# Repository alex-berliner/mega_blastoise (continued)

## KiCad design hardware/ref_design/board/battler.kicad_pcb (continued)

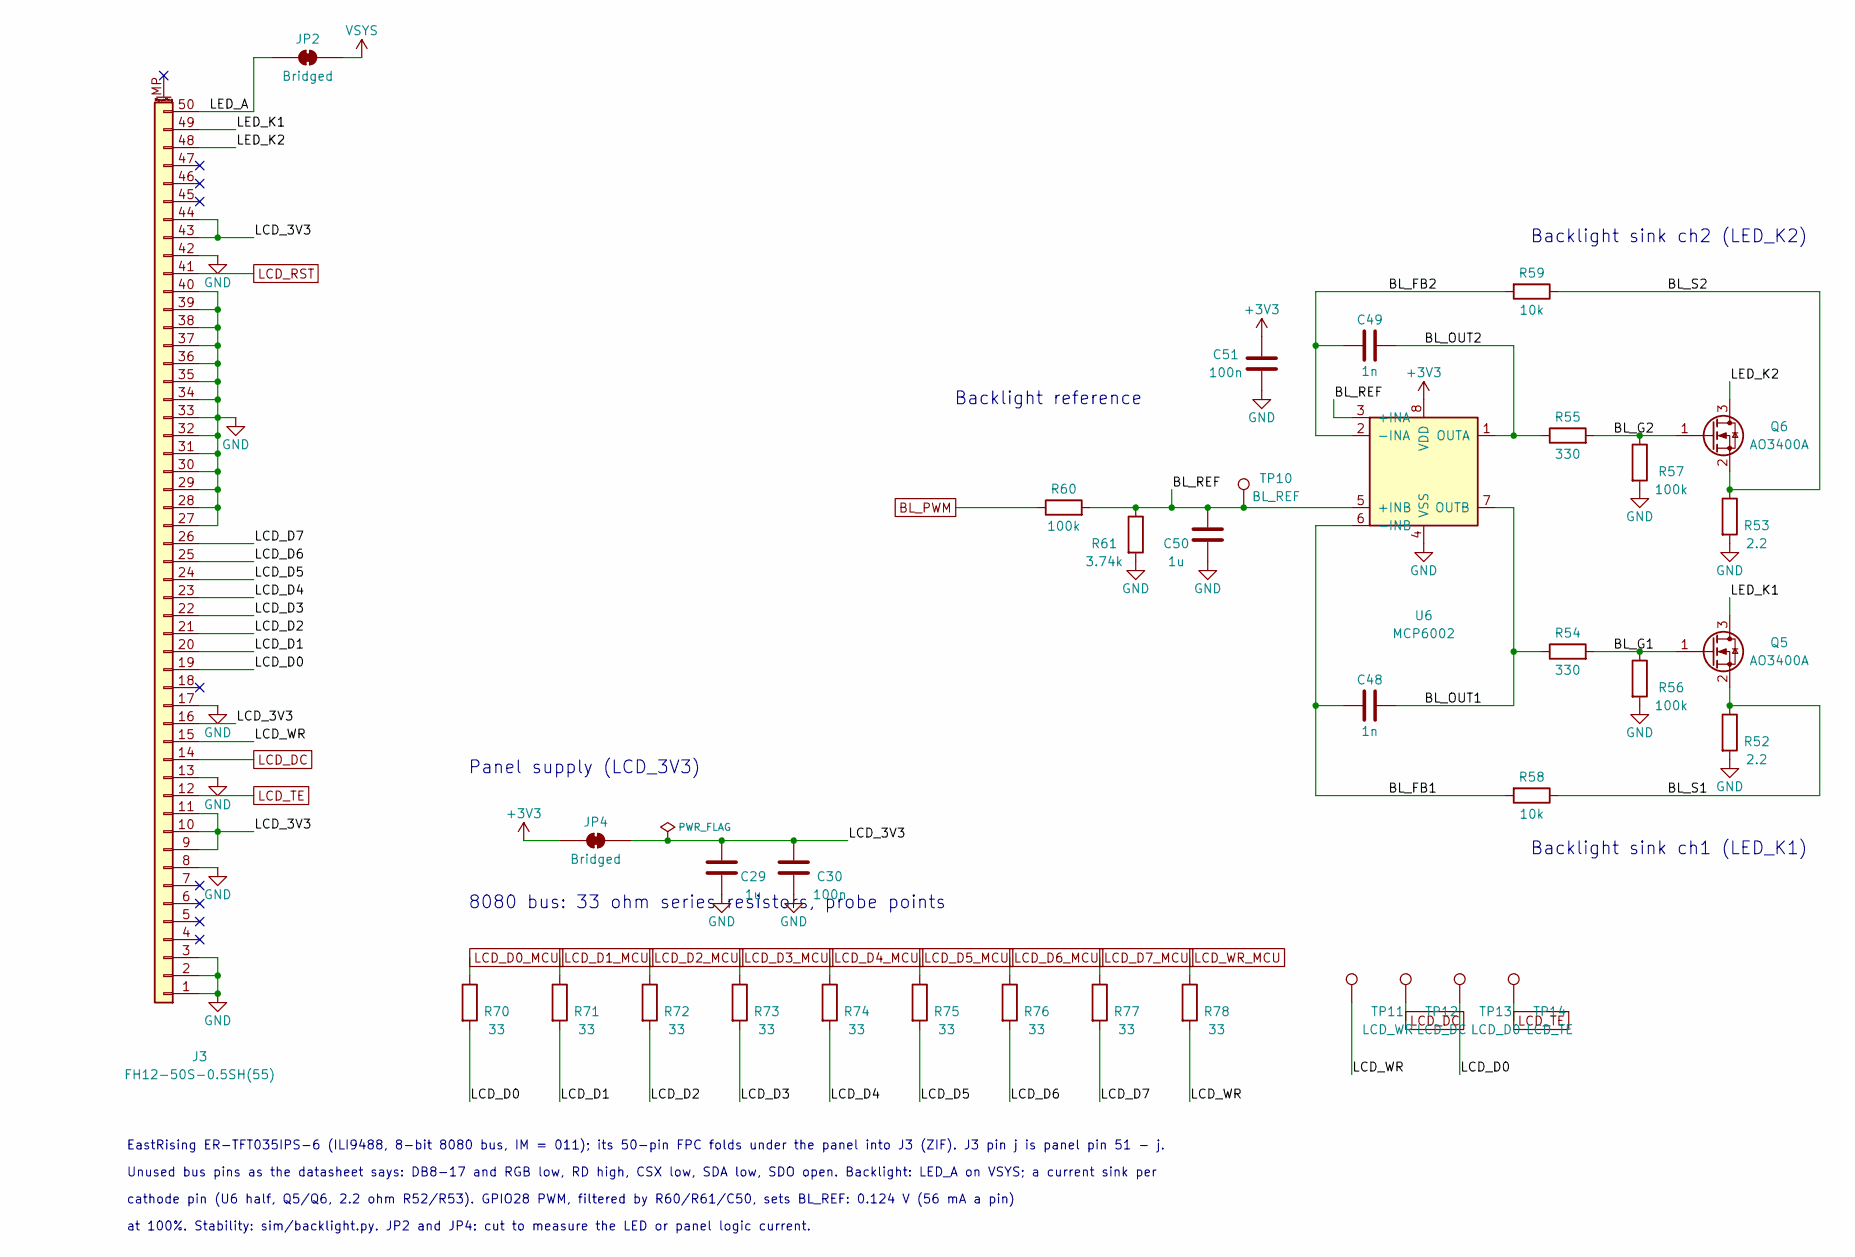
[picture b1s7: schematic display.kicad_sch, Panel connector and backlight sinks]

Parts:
C29, C50: 1u; C_0402_1005Metric; MPN CL05A105KA5NQNC; LCSC C52923
C30, C51: 100n; C_0402_1005Metric; MPN CL05B104KO5NNNC; LCSC C1525
C48, C49: 1n; C_0402_1005Metric; MPN 0402B102K500NT; LCSC C1523
J3: FH12-50S-0.5SH(55); Hirose_FH12-50S-0.5SH_1x50-1MP_P0.50mm_Horizontal; MPN FH12-50S-0.5SH(55); LCSC C202116
JP2, JP4: Bridged; SolderJumper-2_P1.3mm_Bridged_Pad1.0x1.5mm
Q5, Q6: AO3400A; SOT-23; MPN AO3400A; LCSC C20917
R52, R53: 2.2; R_0603_1608Metric; MPN 0603WAF220KT5E; LCSC C22939
R54, R55: 330; R_0402_1005Metric; MPN 0402WGF3300TCE; LCSC C25104
R56, R57, R60: 100k; R_0402_1005Metric; MPN 0402WGF1003TCE; LCSC C25741
R58, R59: 10k; R_0402_1005Metric; MPN 0402WGF1002TCE; LCSC C25744
R61: 3.74k; R_0402_1005Metric; MPN 0402WGF3741TCE; LCSC C15172
R70, R71, R72, R73, R74, R75, R76, R77, R78: 33; R_0402_1005Metric; MPN 0402WGF330JTCE; LCSC C25105
TP10: BL_REF; TestPoint_Pad_D1.0mm
TP11: LCD_WR; TestPoint_Pad_D1.0mm
TP12: LCD_DC; TestPoint_Pad_D1.0mm
TP13: LCD_D0; TestPoint_Pad_D1.0mm
TP14: LCD_TE; TestPoint_Pad_D1.0mm
U6: MCP6002; SOIC-8_3.9x4.9mm_P1.27mm; MPN MCP6002T-I/SN; LCSC C7377

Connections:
+3V3: C51.1, JP4.1 (A), U6.8 (VDD); also elsewhere on the board
/Display/BL_FB1: C48.2, R58.2, U6.6 (-INB)
/Display/BL_FB2: C49.2, R59.2, U6.2 (-INA)
/Display/BL_G1: Q5.1 (G), R54.2, R56.1
/Display/BL_G2: Q6.1 (G), R55.2, R57.1
/Display/BL_OUT1: C48.1, R54.1, U6.7 (OUTB)
/Display/BL_OUT2: C49.1, R55.1, U6.1 (OUTA)
/Display/BL_REF: C50.1, R60.2, R61.1, TP10.1, U6.3 (+INA), U6.5 (+INB)
/Display/BL_S1: Q5.2 (S), R52.1, R58.1
/Display/BL_S2: Q6.2 (S), R53.1, R59.1
/Display/LCD_3V3: C29.1, C30.1, J3.9, J3.10, J3.11, J3.16, J3.43, J3.44, JP4.2 (B)
/Display/LCD_D0: J3.19, R70.2, TP13.1
/Display/LCD_D1: J3.20, R71.2
/Display/LCD_D2: J3.21, R72.2
/Display/LCD_D3: J3.22, R73.2
/Display/LCD_D4: J3.23, R74.2
/Display/LCD_D5: J3.24, R75.2
/Display/LCD_D6: J3.25, R76.2
/Display/LCD_D7: J3.26, R77.2
/Display/LCD_WR: J3.15, R78.2, TP11.1
/Display/LED_A: J3.50, JP2.2 (B)
/Display/LED_K1: J3.49, Q5.3 (D)
/Display/LED_K2: J3.48, Q6.3 (D)
BL_PWM: R60.1; also elsewhere on the board
GND: C29.2, C30.2, C50.2, C51.2, J3.1, J3.2, J3.3, J3.8, J3.13, J3.17, J3.27, J3.28, J3.29, J3.30, J3.31, J3.32, J3.33, J3.34, J3.35, J3.36, J3.37, J3.38, J3.39, J3.40, J3.42, R52.2, R53.2, R56.2, R57.2, R61.2, U6.4 (VSS); also elsewhere on the board
LCD_D0_MCU: R70.1; also elsewhere on the board
LCD_D1_MCU: R71.1; also elsewhere on the board
LCD_D2_MCU: R72.1; also elsewhere on the board
LCD_D3_MCU: R73.1; also elsewhere on the board
LCD_D4_MCU: R74.1; also elsewhere on the board
LCD_D5_MCU: R75.1; also elsewhere on the board
LCD_D6_MCU: R76.1; also elsewhere on the board
LCD_D7_MCU: R77.1; also elsewhere on the board
LCD_DC: J3.14, TP12.1; also elsewhere on the board
LCD_RST: J3.41; also elsewhere on the board
LCD_TE: J3.12, TP14.1; also elsewhere on the board
LCD_WR_MCU: R78.1; also elsewhere on the board
VSYS: JP2.1 (A); also elsewhere on the board

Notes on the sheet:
8080 bus: 33 ohm series resistors, probe points
Panel supply (LCD_3V3)
Backlight reference
Backlight sink ch2 (LED_K2)
Backlight sink ch1 (LED_K1)
EastRising ER-TFT035IPS-6 (ILI9488, 8-bit 8080 bus, IM = 011); its 50-pin FPC folds under the panel into J3 (ZIF). J3 pin j is panel pin 51 - j.
Unused bus pins as the datasheet says: DB8-17 and RGB low, RD high, CSX low, SDA low, SDO open. Backlight: LED_A on VSYS; a current sink per
cathode pin (U6 half, Q5/Q6, 2.2 ohm R52/R53). GPIO28 PWM, filtered by R60/R61/C50, sets BL_REF: 0.124 V (56 mA a pin)
at 100%. Stability: sim/backlight.py. JP2 and JP4: cut to measure the LED or panel logic current.

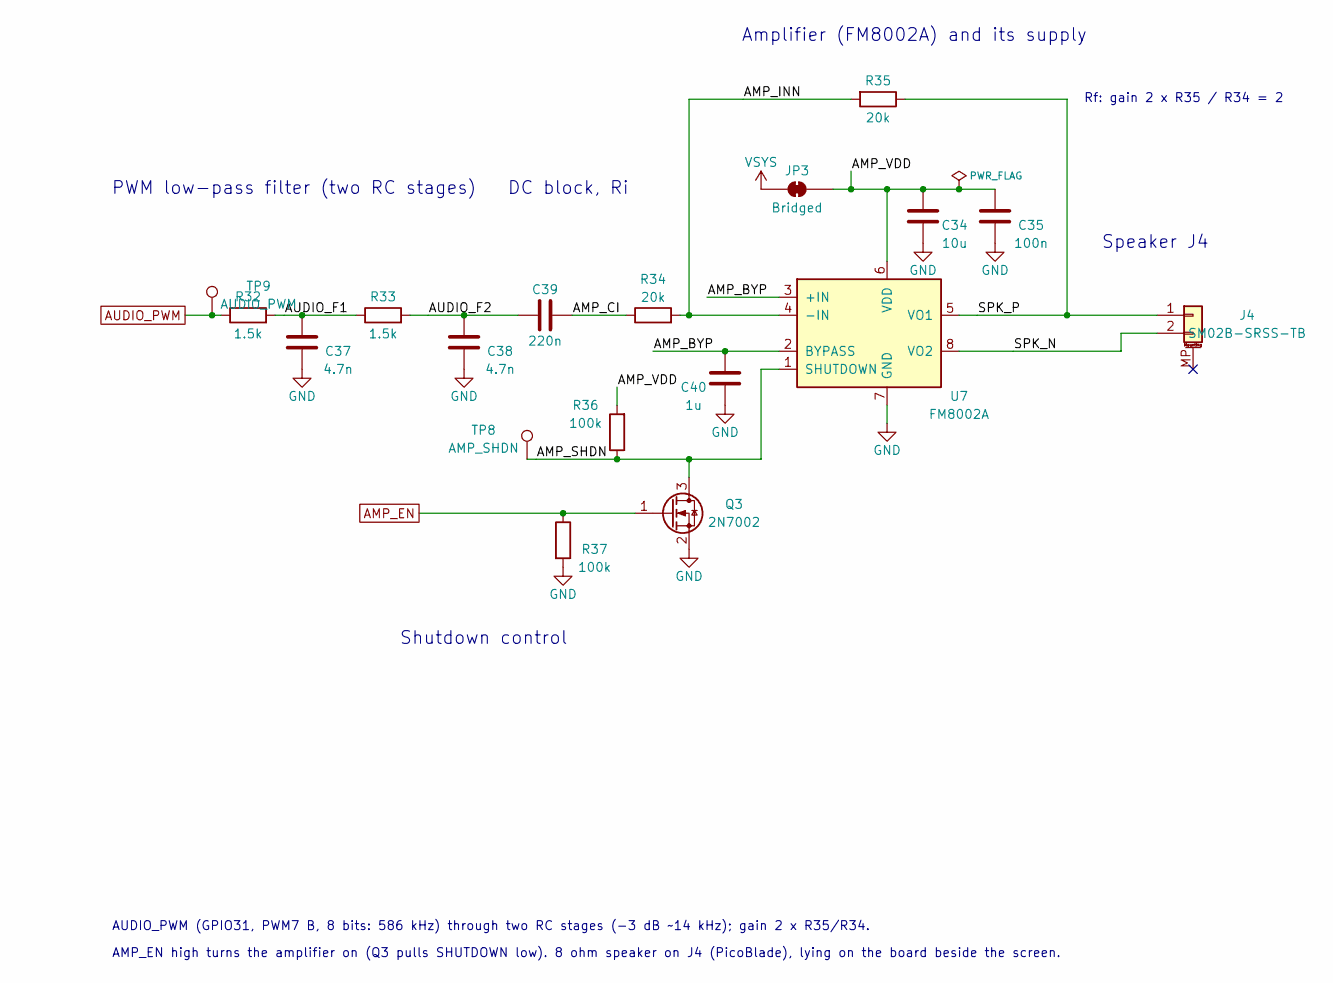
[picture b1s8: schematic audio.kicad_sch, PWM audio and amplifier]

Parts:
C34: 10u; C_0603_1608Metric; MPN CL10A106KP8NNNC; LCSC C19702
C35: 100n; C_0402_1005Metric; MPN CL05B104KO5NNNC; LCSC C1525
C37, C38: 4.7n; C_0402_1005Metric; MPN 0402B472K500NT; LCSC C1538
C39: 220n; C_0402_1005Metric; MPN CL05B224KO5NNNC; LCSC C16772
C40: 1u; C_0402_1005Metric; MPN CL05A105KA5NQNC; LCSC C52923
J4: SM02B-SRSS-TB; JST_SH_SM02B-SRSS-TB_1x02-1MP_P1.00mm_Horizontal; MPN SM02B-SRSS-TB(LF)(SN); LCSC C160402
JP3: Bridged; SolderJumper-2_P1.3mm_Bridged_Pad1.0x1.5mm
Q3: 2N7002; SOT-23; MPN 2N7002; LCSC C8545
R32, R33: 1.5k; R_0402_1005Metric; MPN 0402WGF1501TCE; LCSC C25867
R34, R35: 20k; R_0402_1005Metric; MPN 0402WGF2002TCE; LCSC C25765
R36, R37: 100k; R_0402_1005Metric; MPN 0402WGF1003TCE; LCSC C25741
TP8: AMP_SHDN; TestPoint_Pad_D1.0mm
TP9: AUDIO_PWM; TestPoint_Pad_D1.0mm
U7: FM8002A; SOIC-8_3.9x4.9mm_P1.27mm; MPN FM8002A; LCSC C94625

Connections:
/Audio/AMP_BYP: C40.1, U7.2 (BYPASS), U7.3 (+IN)
/Audio/AMP_CI: C39.2, R34.1
/Audio/AMP_INN: R34.2, R35.2, U7.4 (-IN)
/Audio/AMP_SHDN: Q3.3 (D), R36.1, TP8.1, U7.1 (SHUTDOWN)
/Audio/AMP_VDD: C34.1, C35.1, JP3.2 (B), R36.2, U7.6 (VDD)
/Audio/AUDIO_F1: C37.1, R32.2, R33.1
/Audio/AUDIO_F2: C38.1, C39.1, R33.2
/Audio/SPK_N: J4.2, U7.8 (VO2)
/Audio/SPK_P: J4.1, R35.1, U7.5 (VO1)
AMP_EN: Q3.1 (G), R37.1; also elsewhere on the board
AUDIO_PWM: R32.1, TP9.1; also elsewhere on the board
GND: C34.2, C35.2, C37.2, C38.2, C40.2, Q3.2 (S), R37.2, U7.7 (GND); also elsewhere on the board
VSYS: JP3.1 (A); also elsewhere on the board

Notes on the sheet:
PWM low-pass filter (two RC stages)
DC block, Ri
Rf: gain 2 x R35 / R34 = 2
Amplifier (FM8002A) and its supply
Shutdown control
Speaker J4
AUDIO_PWM (GPIO31, PWM7 B, 8 bits: 586 kHz) through two RC stages (-3 dB ~14 kHz); gain 2 x R35/R34.
AMP_EN high turns the amplifier on (Q3 pulls SHUTDOWN low). 8 ohm speaker on J4 (PicoBlade), lying on the board beside the screen.

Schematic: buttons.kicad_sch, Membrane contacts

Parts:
C52, C53, C62: 100n; C_0402_1005Metric; MPN CL05B104KO5NNNC; LCSC C1525
R63, R86, R87, R88: 47k; R_0402_1005Metric; MPN 0402WGF4702TCE; LCSC C25792
R65: 33; R_0402_1005Metric; MPN 0402WGF330JTCE; LCSC C25105
RN1, RN2, RN3, RN4: 47k; R_Array_Convex_4x0402; MPN 4D02WGJ0473TCE; LCSC C2028
SW1: P1 UP; DSL_button_4ring
SW2: P1 DOWN; DSL_button_4ring
SW3: P1 LEFT; DSL_button_4ring
SW4: P1 RIGHT; DSL_button_4ring
SW5: P1 A; DSL_button_4ring
SW6: P1 B; DSL_button_4ring
SW7: P1 X; DSL_button_4ring
SW8: P1 Y; DSL_button_4ring
SW9: P2 UP; DSL_button_4ring
SW10: P2 DOWN; DSL_button_4ring
SW11: P2 LEFT; DSL_button_4ring
SW12: P2 RIGHT; DSL_button_4ring
SW13: P2 A; DSL_button_4ring
SW14: P2 B; DSL_button_4ring
SW15: P2 X; DSL_button_4ring
SW16: P2 Y; DSL_button_4ring
SW20: P1 SELECT; Dome_4mm_Round
SW21: P1 START; Dome_4mm_Round
SW22: P2 SELECT; Dome_4mm_Round
SW23: P2 START; Dome_4mm_Round
SW24: POWER; Tact_ROCPU_TPS850; MPN TPS850 J14K V SMTR LFS; LCSC C2759975
U8, U9, U11: SN74HC165PWR; TSSOP-16_4.4x5mm_P0.65mm; MPN SN74HC165PWR; LCSC C43420

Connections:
+3V3: C52.1, C53.1, C62.1, R63.1, R86.1, R87.1, R88.1, RN1.5 (R4.2), RN1.6 (R3.2), RN1.7 (R2.2), RN1.8 (R1.2), RN2.5 (R4.2), RN2.6 (R3.2), RN2.7 (R2.2), RN2.8 (R1.2), RN3.5 (R4.2), RN3.6 (R3.2), RN3.7 (R2.2), RN3.8 (R1.2), RN4.5 (R4.2), RN4.6 (R3.2), RN4.7 (R2.2), RN4.8 (R1.2), U8.16 (VCC), U9.16 (VCC), U11.10 (DS), U11.11 (D0), U11.16 (VCC); also elsewhere on the board
/Buttons/P1_A: RN2.1 (R1.1), SW5.1, U8.3 (D4)
/Buttons/P1_B: RN2.2 (R2.1), SW6.1, U8.4 (D5)
/Buttons/P1_DOWN: RN1.2 (R2.1), SW2.1, U8.12 (D1)
/Buttons/P1_LEFT: RN1.3 (R3.1), SW3.1, U8.13 (D2)
/Buttons/P1_RIGHT: RN1.4 (R4.1), SW4.1, U8.14 (D3)
/Buttons/P1_SELECT: R86.2, SW20.1, U11.4 (D5)
/Buttons/P1_START: R88.2, SW21.1, U11.12 (D1)
/Buttons/P1_UP: RN1.1 (R1.1), SW1.1, U8.11 (D0)
/Buttons/P1_X: RN2.3 (R3.1), SW7.1, U8.5 (D6)
/Buttons/P1_Y: RN2.4 (R4.1), SW8.1, U8.6 (D7)
/Buttons/P2_A: RN4.1 (R1.1), SW13.1, U9.3 (D4)
/Buttons/P2_B: RN4.2 (R2.1), SW14.1, U9.4 (D5)
/Buttons/P2_DOWN: RN3.2 (R2.1), SW10.1, U9.12 (D1)
/Buttons/P2_LEFT: RN3.3 (R3.1), SW11.1, U9.13 (D2)
/Buttons/P2_RIGHT: RN3.4 (R4.1), SW12.1, U9.14 (D3)
/Buttons/P2_SELECT: R87.2, SW22.1, U11.3 (D4)
/Buttons/P2_START: R63.2, SW23.1, U11.5 (D6)
/Buttons/P2_UP: RN3.1 (R1.1), SW9.1, U9.11 (D0)
/Buttons/P2_X: RN4.3 (R3.1), SW15.1, U9.5 (D6)
/Buttons/P2_Y: RN4.4 (R4.1), SW16.1, U9.6 (D7)
/Buttons/SR_CHAIN: U8.10 (DS), U9.9 (Q7)
/Buttons/SR_CHAIN2: U9.10 (DS), U11.9 (Q7)
/Buttons/SR_CLK: R65.2, U8.2 (CP), U9.2 (CP), U11.2 (CP)
CHG_PG_N: U11.13 (D2); also elsewhere on the board
CHG_STAT_N: U11.14 (D3); also elsewhere on the board
GND: C52.2, C53.2, C62.2, SW1.2, SW2.2, SW3.2, SW4.2, SW5.2, SW6.2, SW7.2, SW8.2, SW9.2, SW10.2, SW11.2, SW12.2, SW13.2, SW14.2, SW15.2, SW16.2, SW20.2, SW21.2, SW22.2, SW23.2, U8.8 (GND), U8.15 (~CE), U9.8 (GND), U9.15 (~CE), U11.8 (GND), U11.15 (~CE); also elsewhere on the board
PWR_BTN_N: U11.6 (D7); also elsewhere on the board
PWR_BTN_RAW: SW24.1; also elsewhere on the board
SR_CLK_MCU: R65.1; also elsewhere on the board
SR_DATA: U8.9 (Q7); also elsewhere on the board
SR_PL: U8.1 (~PL), U9.1 (~PL), U11.1 (~PL); also elsewhere on the board
VSYS: SW24.2; also elsewhere on the board

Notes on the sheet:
Seat 1: D-pad and face buttons
Seat 2: D-pad and face buttons
Seat 1 Start/Select, power
SW24 is the power button: it joins VSYS to
PWR_BTN_RAW (Power sheet); the MCU reads it
through Q1 as PWR_BTN_N (bit 16).
Seat 2 Start/Select
Third register: Start/Select and charger status
SR_CLK source termination
D-pad and face buttons: bare ENIG combs under DS Lite silicone, read through a 74HC165 per seat (chained: U11 to U9 to U8, U9's
Q7 into U8's DS; SR_PL low loads, 16 SR_CLK rises shift P1 Y..UP then P2 Y..UP out of SR_DATA, low = pressed; 8 more give U11).
Start/Select: 4 mm metal domes (HYP 600-415S-260), read by U11 (24-clock read: the extra 8 bits: power, Starts, Selects, charger); their contacts go to GND, 47k pull-ups. The power button is SW24.

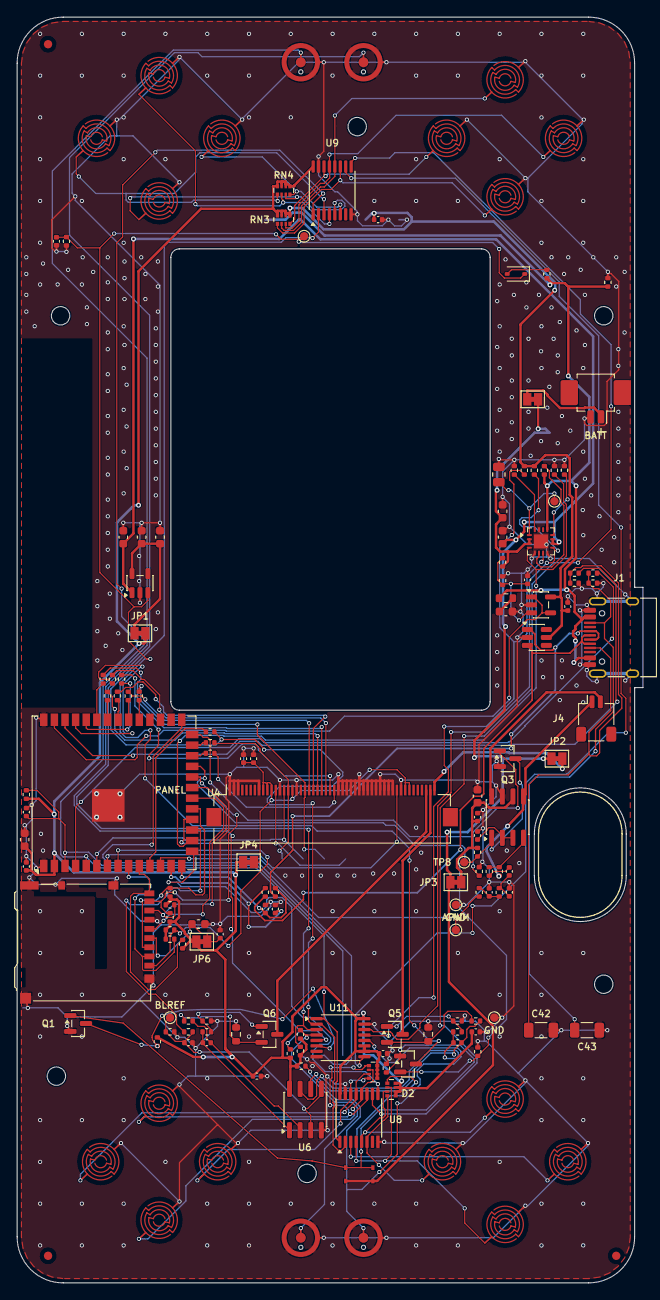
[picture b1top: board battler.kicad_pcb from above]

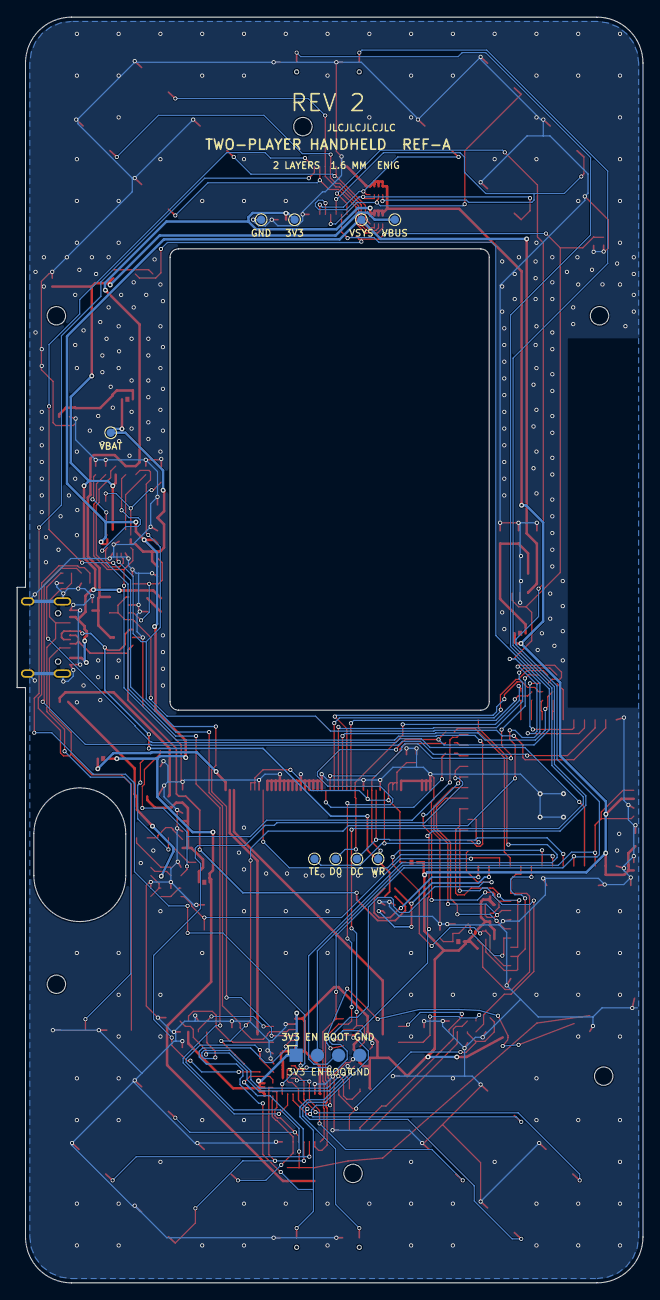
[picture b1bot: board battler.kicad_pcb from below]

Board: 2 copper layers, 74.9 x 151.5 mm, 170 parts (10 on the bottom side), 112 nets.

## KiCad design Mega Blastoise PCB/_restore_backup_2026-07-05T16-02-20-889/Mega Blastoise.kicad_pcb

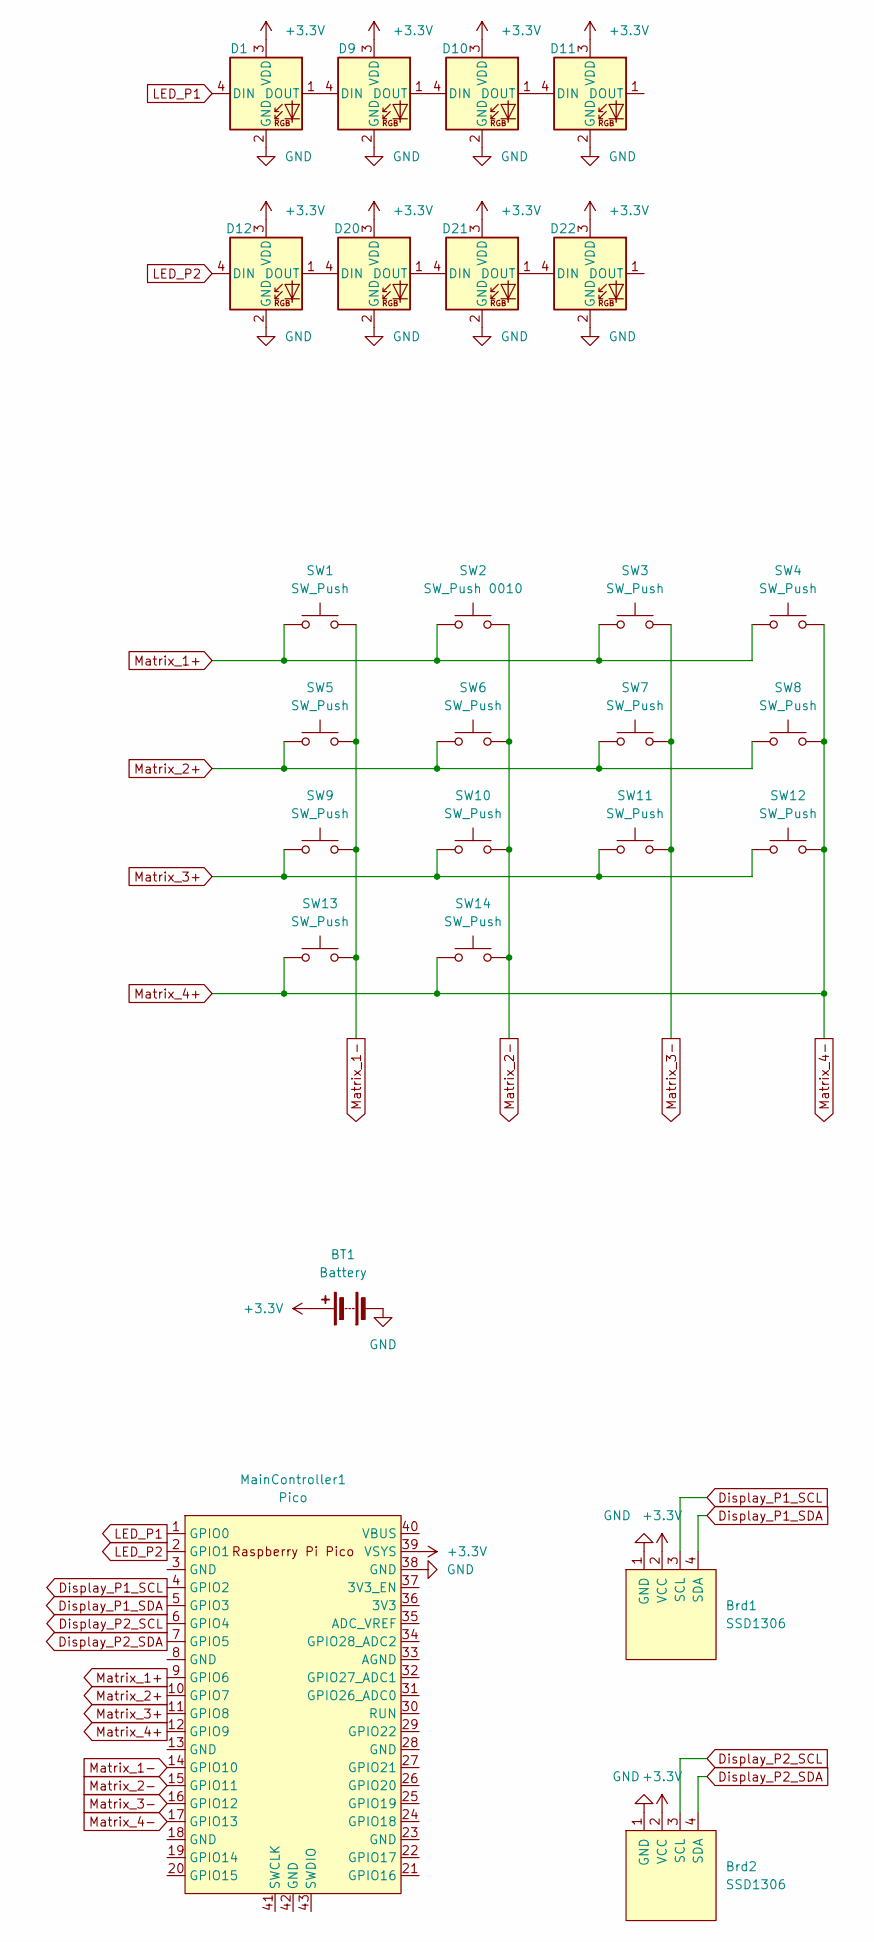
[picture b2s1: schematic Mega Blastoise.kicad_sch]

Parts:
BT1: Battery; PinHeader_1x02_P2.54mm_Vertical
Brd1, Brd2: SSD1306; PinHeader_1x04_P2.54mm_Vertical
D1, D12: NeoPixel_THT; neopixel 8 stick
D9, D10, D11, D20, D21, D22: NeoPixel_THT; Neopixel Breadboard
MainController1: Pico; RPi_Pico_SMD_TH
SW1, SW3, SW4, SW5, SW6, SW7, SW8, SW9, SW10, SW11, SW12, SW13, SW14: SW_Push; SW_PUSH-12mm
SW2: SW_Push 0010; SW_PUSH-12mm

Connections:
+3.3V: BT1.1 (+), Brd1.2 (VCC), Brd2.2 (VCC), D1.3 (VDD), D9.3 (VDD), D10.3 (VDD), D11.3 (VDD), D12.3 (VDD), D20.3 (VDD), D21.3 (VDD), D22.3 (VDD), MainController1.39 (VSYS)
Display_P1_SCL: Brd1.3 (SCL), MainController1.4 (GPIO2)
Display_P1_SDA: Brd1.4 (SDA), MainController1.5 (GPIO3)
Display_P2_SCL: Brd2.3 (SCL), MainController1.6 (GPIO4)
Display_P2_SDA: Brd2.4 (SDA), MainController1.7 (GPIO5)
GND: BT1.2 (-), Brd1.1 (GND), Brd2.1 (GND), D1.2 (GND), D9.2 (GND), D10.2 (GND), D11.2 (GND), D12.2 (GND), D20.2 (GND), D21.2 (GND), D22.2 (GND), MainController1.38 (GND)
LED_P1: D1.4 (DIN), MainController1.1 (GPIO0)
LED_P2: D12.4 (DIN), MainController1.2 (GPIO1)
Matrix_1+: MainController1.9 (GPIO6), SW1.1, SW2.1, SW3.1, SW4.1
Matrix_1-: MainController1.14 (GPIO10), SW1.2, SW5.2, SW9.2, SW13.2
Matrix_2+: MainController1.10 (GPIO7), SW5.1, SW6.1, SW7.1, SW8.1
Matrix_2-: MainController1.15 (GPIO11), SW2.2, SW6.2, SW10.2, SW14.2
Matrix_3+: MainController1.11 (GPIO8), SW9.1, SW10.1, SW11.1, SW12.1
Matrix_3-: MainController1.16 (GPIO12), SW3.2, SW7.2, SW11.2
Matrix_4+: MainController1.12 (GPIO9), MainController1.17 (GPIO13), SW4.2, SW8.2, SW12.2, SW13.1, SW14.1
unnamed: D1.1 (DOUT), D9.4 (DIN)
unnamed: D9.1 (DOUT), D10.4 (DIN)
unnamed: D10.1 (DOUT), D11.4 (DIN)
unnamed: D12.1 (DOUT), D20.4 (DIN)
unnamed: D20.1 (DOUT), D21.4 (DIN)
unnamed: D21.1 (DOUT), D22.4 (DIN)

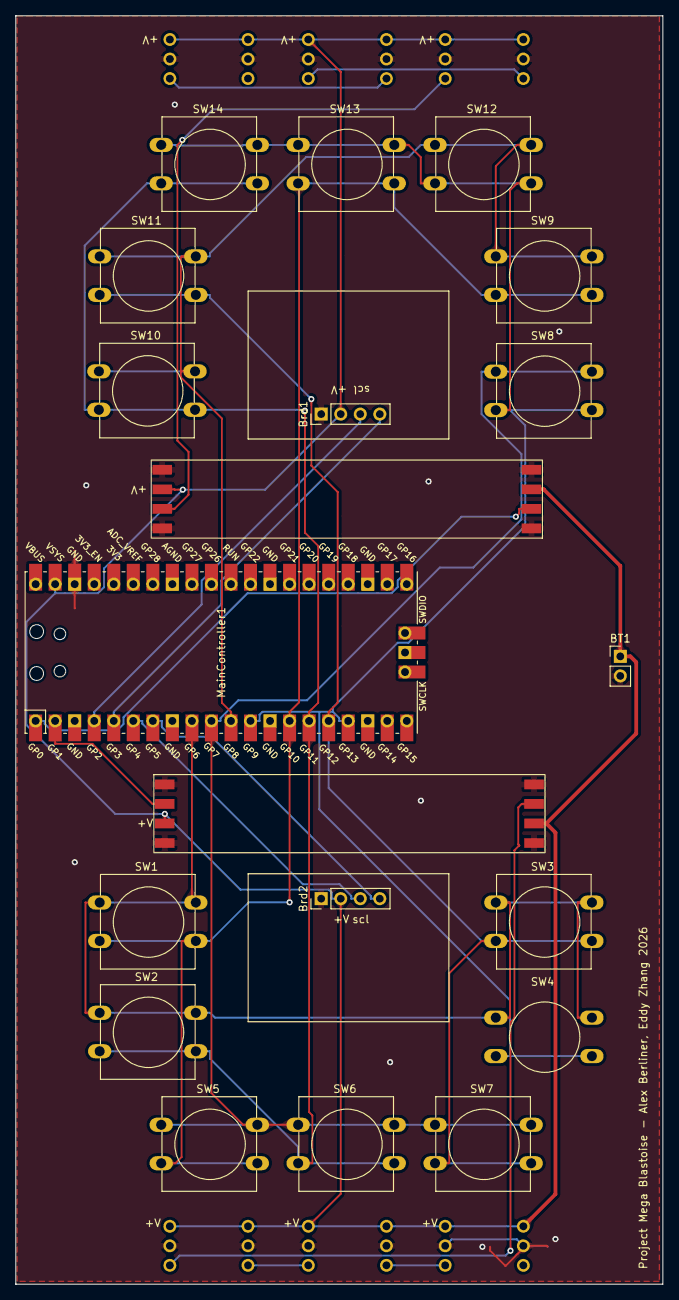
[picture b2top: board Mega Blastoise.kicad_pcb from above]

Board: 2 copper layers, 84.1 x 164.9 mm, 26 parts (0 on the bottom side), 21 nets.

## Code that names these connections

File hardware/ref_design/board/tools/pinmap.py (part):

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ROLE = {
    "PWR_HOLD": "output: set high to stay on (see Power control); low turns the device off once the button is up",
    "AUDIO_PWM": "LEDC, 8 bits at 312.5 kHz (80 MHz / 256): audio through two RC stages (-3 dB at 6.7 kHz) into U7 (see Audio)",
    "AMP_EN": "output: high turns the FM8002A on (Q3 pulls its SHUTDOWN low); strapping pin, low at reset (R37 100k)",
    "CHG_OFF": "output: the BQ24073's CE, high stops charging; strapping pin, low at reset (R44 4.7k pulls it low)",
    "SR_PL": "output: the 74HC165s' SH/LD (U8, U9, U11 pin 1): low loads the 24 inputs, high to shift them out",
    "SR_CLK_MCU": "output: the 74HC165s' clock (SR_CLK) through R65 (33 ohm, at the module end); each rising edge shifts one bit",
    "SR_DATA": "input: U8's Q7, the end of the chain: 24 bits, low = pressed (see Buttons); strapping pin IO3 (JTAG source: leave the eFuse alone)",
    "LCD_DC": "display data/command (D/CX), straight to the panel",
    "LCD_RST": "display reset, active low",
    "LCD_TE": "input: the panel's tearing-effect signal (enable with TEON); start a frame on its edge",
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    "CC1_SENSE": "ADC1_CH1: USB-C CC1 through 10k; the source's current offer",
    "CC2_SENSE": "ADC1_CH3: USB-C CC2 through 10k",
    "BOOT": "strapping pin IO0: J7 pad (no button); low at reset enters the ROM's download mode; free as an input afterwards",
    "SD_CMD": "SDMMC CMD (GPIO matrix), 10k pull-up R79", "SD_CLK": "SDMMC CLK (GPIO matrix)",
    "SD_D0": "SDMMC D0, 10k pull-up R80", "SD_D1": "SDMMC D1, 10k pull-up R83", "SD_D2": "SDMMC D2, 10k pull-up R81",
    "SD_D3": "SDMMC D3, 10k pull-up R82", "SD_CD": "card detect: low with a card in, 10k pull-up R84",
    "USB_DM_MCU": "USB D- (IO19, the ROM's USB Serial/JTAG too), 22 ohm R22 to the connector",
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        "## Storage (microSD)",
        "",
        "J8 is a push-pull-free push-push slot with a card-detect switch (SD_CD low = card in, 10k pull-up). 4-bit SDMMC through the",
        f"GPIO matrix: CMD IO{G['SD_CMD']}, CLK IO{G['SD_CLK']}, D0-D3 IO{G['SD_D0']}-IO{G['SD_D3']}, CD IO{G['SD_CD']}; 10k pull-ups on CMD, D0-D3 and CD. The card's supply",
        "SD_VDD comes from 3V3 through JP6 (cut it to measure the card's current). 3.3 V signalling only.",
        "",
        "## Buttons",
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        "Each seat's D-pad and A/B/X/Y (8 contacts to GND) come in through a 74HC165 at that seat (U8 seat 1, U9 seat 2);",
        "a third register U11 carries the Starts, the Selects and the charger's two status lines. The chain is",
        "U11 -> U9 -> U8 -> SR_DATA, 24 bits. A read: SR_PL low then high (parallel load), then 24 rising edges on",
        f"GPIO{G['SR_CLK_MCU']} (SR_CLK through R65); SR_DATA shows each bit before the edge that shifts it: P1 Y first, then P1 X, B, A,",
        "RIGHT, LEFT, DOWN, UP, then seat 2 in the same order (bits 0-15, 1 = released), then U11: bit 16 PWR_BTN_N (the power",
        "button SW24, through Q1: not a Start), 17 P2_START, 18 P1_SELECT, 19 P2_SELECT, 20 CHG_STAT_N, 21 CHG_PG_N, 22 P1_START, 23",
        "always 1. A 16-bit read still works (the first 16 bits are unchanged). Between reads SR_PL rests high and the clock low.",
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        "",
        "## Backlight (current sinks on BL_PWM)",
        "",
        f"GPIO{G['BL_PWM']} runs an LEDC channel, for example 12 bits at 19.5 kHz (80 MHz / 4096). R60/R61/C50 filter",
        "it into BL_REF (0.124 V at 100%, time constant 3.75 ms), and each cathode pin's sink holds",
        "its 2.2 ohm sense resistor at BL_REF: 56 mA a pin at 100% duty, 113 mA for the six LEDs",
        "(the panel's maximum is 120 mA; its typical rating, 15 mA per LED, is 80% duty). The LED",
        "current is DC, so the PWM frequency only sets the ripple (about 0.6% at 19.5 kHz, scaled from the 0.3% at 36.6 kHz",
        "that board/sim/backlight.py gave; not re-simulated). Current is",
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        "",
        "## Audio (LEDC into the FM8002A)",
        "",
        f"GPIO{G['AUDIO_PWM']} is an LEDC channel on its own timer (not the backlight's). Run it at 8 bits: at 80 MHz that's a 312.5 kHz carrier, which R32/C37 and",
        "R33/C38 (1.5k, 4.7 nF; board/sim/audio_filter.py) take 46 dB down, with the audio band -3 dB at about 6.7 kHz. Not 10 bits:",
        "78 kHz would sit much nearer the audio band (dither or noise-shape for more resolution). C39",
        "blocks the DC, and U7 drives the speaker bridge-tied at about 1.8x (R35/R34, with the filter's",
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        "",
        "## Battery voltage",
        "",
        f"VBAT = 2 x the ADC1 reading on GPIO{G['VBAT_SENSE']} (ADC1_CH0; ADC1 only: ADC2 cannot be used while Wi-Fi runs), 12-bit, attenuation",
        "12 dB (input range about 0 to 3.1 V; full charge reads about 2.10 V at the pin), with the eFuse calibration. Unlike the",
        "RP2350 board, the ADC does not use the 3V3 rail as its reference. Full charge reads about 2.10 V at the pin.",
        "",
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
